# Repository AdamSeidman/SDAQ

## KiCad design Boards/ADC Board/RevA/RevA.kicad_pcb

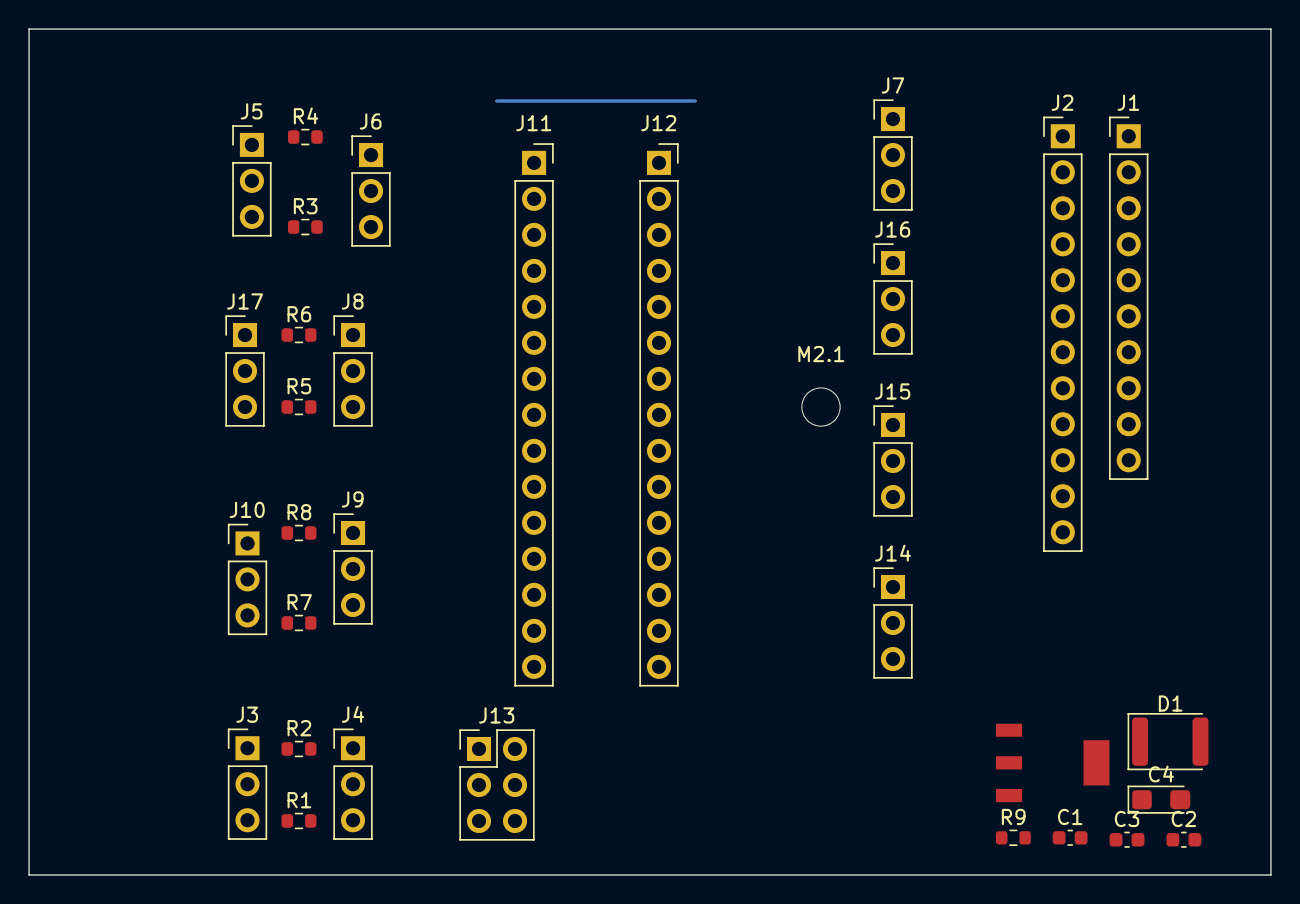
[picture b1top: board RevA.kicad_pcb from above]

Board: 2 copper layers, 87.6 x 59.7 mm, 33 parts (0 on the bottom side), 26 nets.

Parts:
C1: 0.1uF; C_0603_1608Metric
C2: 1uF; C_0603_1608Metric
C3: 1uF_cpu; C_0603_1608Metric
C4: 4.7uF_16V_cpu; CP_EIA-3216-18_Kemet-A
D1: LED; LED_1812_4532Metric
J1: Left Connector; PinHeader_1x10_P2.54mm_Vertical
J2: Right Connector; PinHeader_1x12_P2.54mm_Vertical
J3, J5, J7, J9, J14, J15, J16, J17: Screw Terminals; PinHeader_1x03_P2.54mm_Vertical
J4, J6, J8, J10: Jumper Terminals; PinHeader_1x03_P2.54mm_Vertical
J11, J12: Arduino Nano; PinSocket_1x15_P2.54mm_Vertical
J13: Extra Pins; PinHeader_2x03_P2.54mm_Vertical
M2.1: CMH; MountingHole_2.7mm_M2.5
R1, R2, R3, R4, R5, R6, R7, R8: 10k; R_0603_1608Metric
R9: 350?; R_0603_1608Metric
VR1: LM1117IMPX-5.0; SOT230P700X180-4N

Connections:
/5V: C2.1, C3.1, C4.1, J1.2, J1.4, J3.3, J5.3, J7.3, J9.3, J12.1, J13.1, J14.3, J15.3, J16.3, J17.3, R1.2, R3.2, R5.2, R7.2, VR1.2, VR1.4
/Analog_0: J12.12, J14.2
/Analog_1: J12.11, J15.2
/Analog_2: J12.10, J16.2
/Analog_3: J12.9, J17.2
/Controller/A6: J12.6, J13.3
/Controller/A7: J12.5, J13.2
/Controller/D11: J11.14, J13.4
/Controller/D12: J11.15, J13.5
/Digital_0: J3.2, J4.2, J11.5
/Digital_1: J5.2, J6.2, J11.6
/Digital_2: J7.2, J8.2, J11.7
/Digital_3: J9.2, J10.2, J11.8
/GND: C1.2, C2.2, C3.2, C4.2, D1.1, J1.6, J1.9, J2.5, J2.10, J3.1, J5.1, J7.1, J9.1, J11.4, J12.2, J13.6, J14.1, J15.1, J16.1, J17.1, R2.2, R4.2, R6.2, R8.2, VR1.1
/I2C_Clock: J1.5, J12.7
/I2C_Data: J1.3, J12.8
/VCC: C1.1, R9.1, VR1.3
unnamed: D1.2, R9.2
unnamed: J4.1, R2.1
unnamed: J4.3, R1.1
unnamed: J6.1, R4.1
unnamed: J6.3, R3.1
unnamed: J8.1, R6.1
unnamed: J8.3, R5.1
unnamed: J10.1, R8.1
unnamed: J10.3, R7.1

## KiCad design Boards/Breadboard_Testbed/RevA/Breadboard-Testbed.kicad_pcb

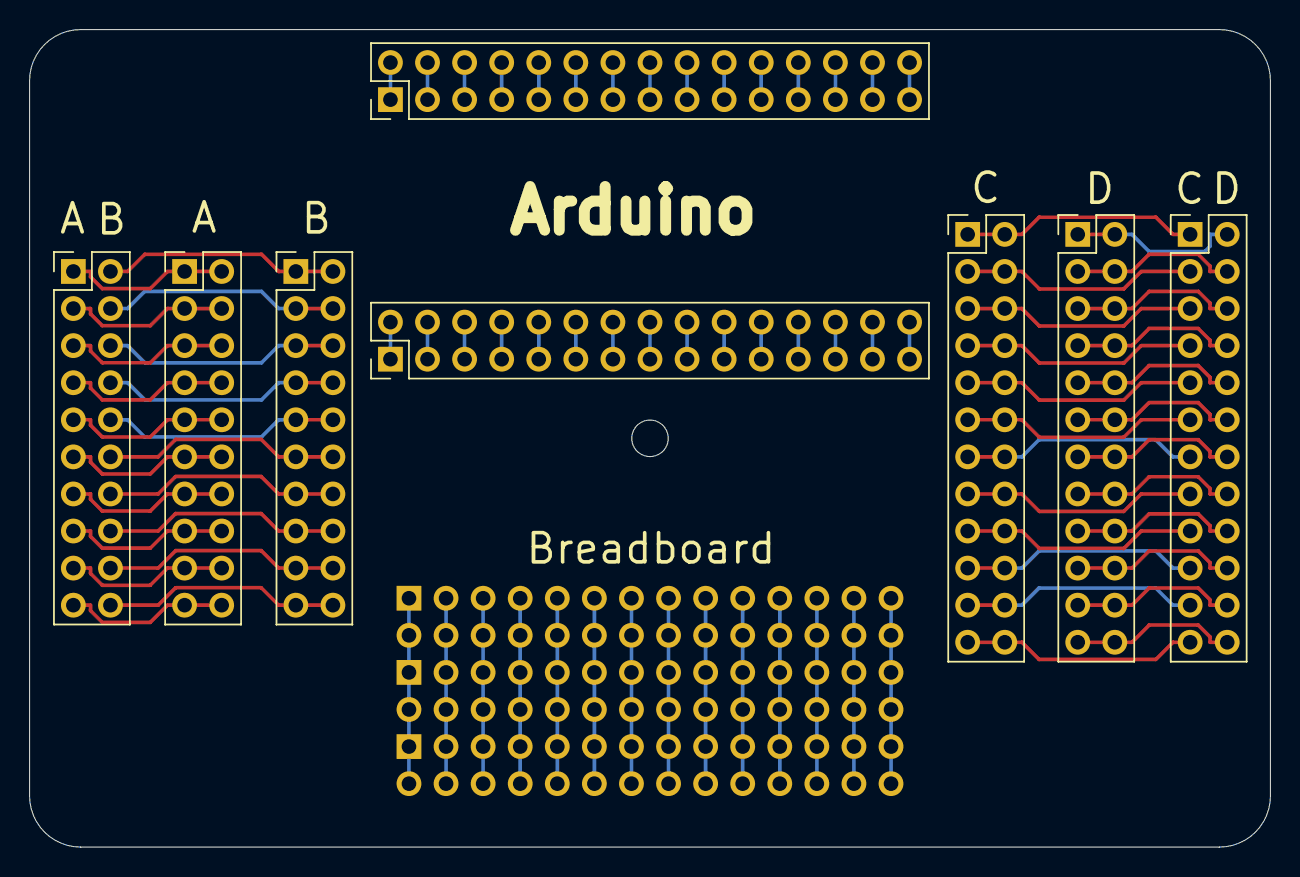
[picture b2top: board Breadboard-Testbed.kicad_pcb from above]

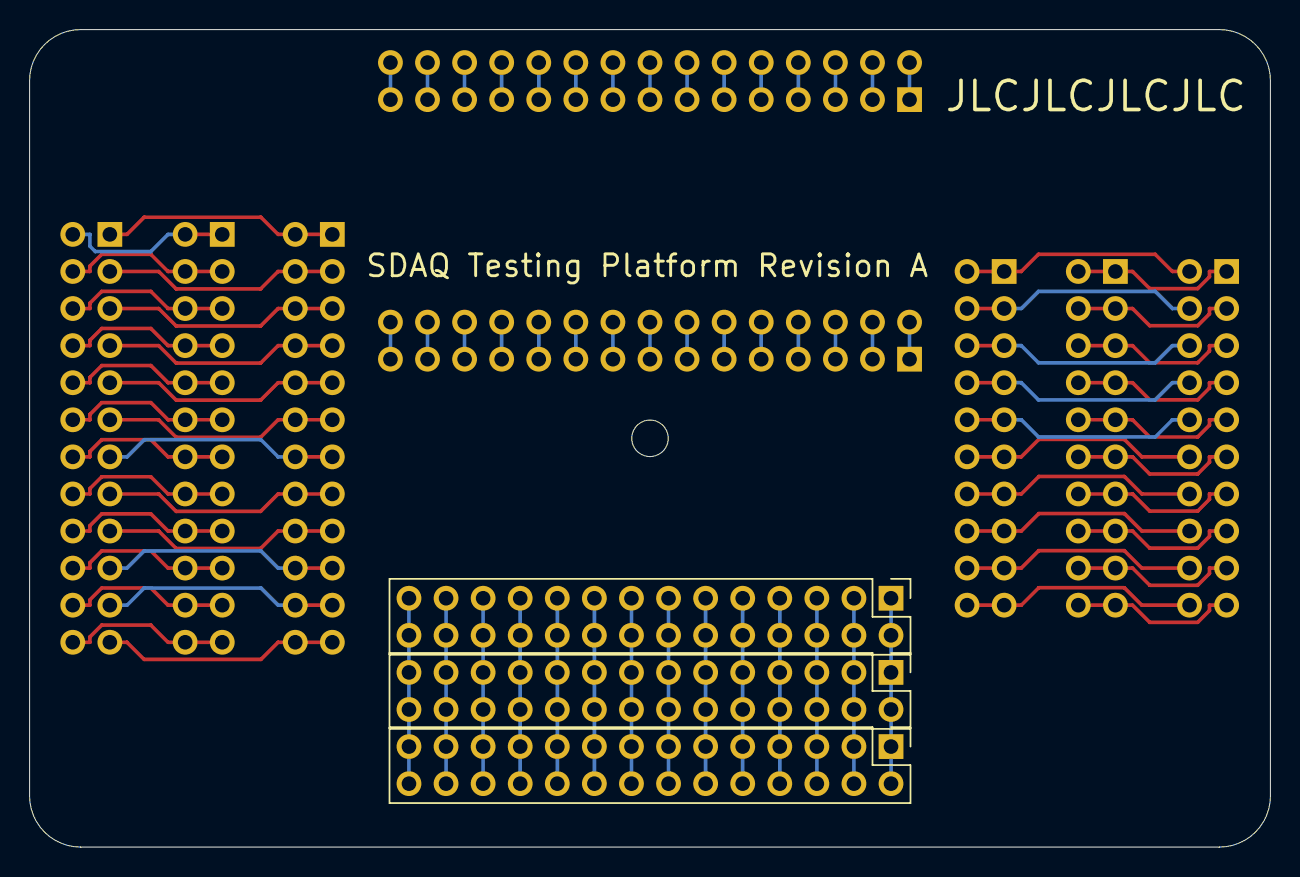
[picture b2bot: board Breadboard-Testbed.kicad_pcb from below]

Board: 2 copper layers, 85.0 x 56.0 mm, 12 parts (3 on the bottom side), 88 nets.

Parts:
H1: CMH; MountingHole_2.5mm
J1: main_conn_10; PinHeader_2x10_P2.54mm_Vertical
J2: main_conn_12; PinHeader_2x12_P2.54mm_Vertical
J3, J4, J6: Conn_02x14_Odd_Even; PinHeader_2x14_P2.54mm_Vertical
J5, J8: Conn_02x10_Counter_Clockwise; PinHeader_2x10_P2.54mm_Vertical
J7: Arduino-left; PinHeader_2x15_P2.54mm_Vertical
J9, J12: Conn_02x12_Counter_Clockwise; PinHeader_2x12_P2.54mm_Vertical
J10: Arduino-right; PinHeader_2x15_P2.54mm_Vertical

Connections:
unnamed: J1.1, J5.1, J5.2
unnamed: J1.2, J8.1, J8.2
unnamed: J1.3, J5.3, J5.4
unnamed: J1.4, J8.3, J8.4
unnamed: J1.5, J5.5, J5.6
unnamed: J1.6, J8.5, J8.6
unnamed: J1.7, J5.7, J5.8
unnamed: J1.8, J8.7, J8.8
unnamed: J1.9, J5.9, J5.10
unnamed: J1.10, J8.9, J8.10
unnamed: J1.11, J5.11, J5.12
unnamed: J1.12, J8.11, J8.12
unnamed: J1.13, J5.13, J5.14
unnamed: J1.14, J8.13, J8.14
unnamed: J1.15, J5.15, J5.16
unnamed: J1.16, J8.15, J8.16
unnamed: J1.17, J5.17, J5.18
unnamed: J1.18, J8.17, J8.18
unnamed: J1.19, J5.19, J5.20
unnamed: J1.20, J8.19, J8.20
unnamed: J2.1, J9.1, J9.2
unnamed: J2.3, J9.3, J9.4
unnamed: J2.5, J9.5, J9.6
unnamed: J2.7, J9.7, J9.8
unnamed: J2.9, J9.9, J9.10
unnamed: J2.11, J9.11, J9.12
unnamed: J2.13, J9.13, J9.14
unnamed: J2.15, J9.15, J9.16
unnamed: J2.17, J9.17, J9.18
unnamed: J2.19, J9.19, J9.20
unnamed: J2.21, J9.21, J9.22
unnamed: J2.23, J9.23, J9.24
unnamed: J3.1, J3.2, J4.1, J4.2, J6.1, J6.2
unnamed: J3.3, J3.4, J4.3, J4.4, J6.3, J6.4
unnamed: J3.5, J3.6, J4.5, J4.6, J6.5, J6.6
unnamed: J3.7, J3.8, J4.7, J4.8, J6.7, J6.8
unnamed: J3.9, J3.10, J4.9, J4.10, J6.9, J6.10
unnamed: J3.11, J3.12, J4.11, J4.12, J6.11, J6.12
unnamed: J3.13, J3.14, J4.13, J4.14, J6.13, J6.14
unnamed: J3.15, J3.16, J4.15, J4.16, J6.15, J6.16
unnamed: J3.17, J3.18, J4.17, J4.18, J6.17, J6.18
unnamed: J3.19, J3.20, J4.19, J4.20, J6.19, J6.20
unnamed: J3.21, J3.22, J4.21, J4.22, J6.21, J6.22
unnamed: J3.23, J3.24, J4.23, J4.24, J6.23, J6.24
unnamed: J3.25, J3.26, J4.25, J4.26, J6.25, J6.26
unnamed: J3.27, J3.28, J4.27, J4.28, J6.27, J6.28
unnamed: J7.1, J7.2
unnamed: J7.3, J7.4
unnamed: J7.5, J7.6
unnamed: J7.7, J7.8
unnamed: J7.9, J7.10
unnamed: J7.11, J7.12
unnamed: J7.13, J7.14
unnamed: J7.15, J7.16
unnamed: J7.17, J7.18
unnamed: J7.19, J7.20
unnamed: J7.21, J7.22
unnamed: J7.23, J7.24
unnamed: J7.25, J7.26
unnamed: J7.27, J7.28
unnamed: J7.29, J7.30
unnamed: J10.1, J10.2
unnamed: J10.3, J10.4
unnamed: J10.5, J10.6
unnamed: J10.7, J10.8
unnamed: J10.9, J10.10
unnamed: J10.11, J10.12
unnamed: J10.13, J10.14
unnamed: J10.15, J10.16
unnamed: J10.17, J10.18
unnamed: J10.19, J10.20
unnamed: J10.21, J10.22
unnamed: J10.23, J10.24
unnamed: J10.25, J10.26
unnamed: J10.27, J10.28
unnamed: J10.29, J10.30
unnamed: J2.2, J12.1, J12.2
unnamed: J2.4, J12.3, J12.4
unnamed: J2.6, J12.5, J12.6
unnamed: J2.8, J12.7, J12.8
unnamed: J2.10, J12.9, J12.10
unnamed: J2.12, J12.11, J12.12
unnamed: J2.14, J12.13, J12.14
unnamed: J2.16, J12.15, J12.16
unnamed: J2.18, J12.17, J12.18
unnamed: J2.20, J12.19, J12.20
unnamed: J2.22, J12.21, J12.22
unnamed: J2.24, J12.23, J12.24

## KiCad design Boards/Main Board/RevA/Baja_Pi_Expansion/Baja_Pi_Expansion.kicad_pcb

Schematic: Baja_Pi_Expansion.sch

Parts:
J1: Conn_02x10_Counter_Clockwise; PinHeader_2x10_P2.54mm_Vertical
J2: Conn_02x12_Counter_Clockwise; PinHeader_2x12_P2.54mm_Vertical
J3: Screw_Terminal_01x04; PinHeader_1x04_P2.54mm_Vertical
J4: Conn_02x20_Odd_Even; PinHeader_2x20_P2.54mm_Vertical
J5: Conn_01x03_Male; PinHeader_1x03_P2.54mm_Vertical
J6: Screw_Terminal_01x06; PinHeader_1x06_P2.54mm_Vertical
R1, R2: 4.7k; R_0603_1608Metric
R3, R4, R5, R6: R_US; R_0603_1608Metric
U1: HDSP-7403; HDSP-7401

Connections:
/3v3: J1.1, J1.17, J4.1, J4.17
/5v: J1.2, J1.4, J4.2, J4.4, J5.1, J6.1, J6.4, R1.1, R2.2, R5.1; also elsewhere on the board
/analog_in: J2.9, J4.29, J6.5
/brakes: J6.7, R3.1
/dig_in: J2.11, J4.31, J5.2, J6.2, R5.2, R6.1
/gnd: J1.6, J1.9, J1.14, J1.20, J2.5, J2.10, J2.14, J2.19, J3.2, J3.4, J4.6, J4.9, J4.14, J4.20, J4.25, J4.30, J4.34, J4.39, J5.3, J6.3, J6.6, R4.2, R6.2, U1.1 (CC), U1.6 (CC); also elsewhere on the board
/gpio1: J1.7, J4.7, R3.2, R4.1
/gpio4: J2.12, J4.32, U1.7 (DP)
/gpio5: J2.13, J4.33, U1.3 (G)
/gpio6: J1.15, J4.15, U1.2 (F)
/gpio7: J1.16, J4.16, U1.4 (E)
/gpio8: J1.18, J4.18, U1.5 (D)
/gpio9: J2.2, J4.22, U1.8 (C)
/gpio10: J2.17, J4.37, U1.9 (B)
/gpio11: J1.13, J4.13, U1.10 (A)
/miso: J2.1, J4.21
/miso2: J2.18, J4.38
/miso2_pwm: J2.15, J4.35
/mosi: J1.19, J4.19
/scl: J2.8, J4.28
/scl2: J1.5, J4.5, R2.1
/sclk: J2.3, J4.23
/sclk2: J2.20, J4.40
/sda: J2.7, J4.27
/sda2: J1.3, J4.3, R1.2
/spi2_ce0: J1.12, J4.12
/spi2_ce1: J1.11, J4.11
/spi_ce0: J2.4, J4.24
/spi_ce1: J2.6, J4.26
/uart_rx: J1.10, J4.10
/uart_tx: J1.8, J4.8
/vcc: J2.23, J2.24, J3.1, J3.3; also elsewhere on the board

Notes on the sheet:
pwm
gpio 14
gpio 15
gpio 17
gpio 8
gpio 7
gpio 1
12 pwm
gpio 16
gpio 20
gpio 21
gpio 10 gpio 9 gpio 11
gpio 0
gpio 11
gpio 10
gpio 9
+20
pwm 12
pin jumper

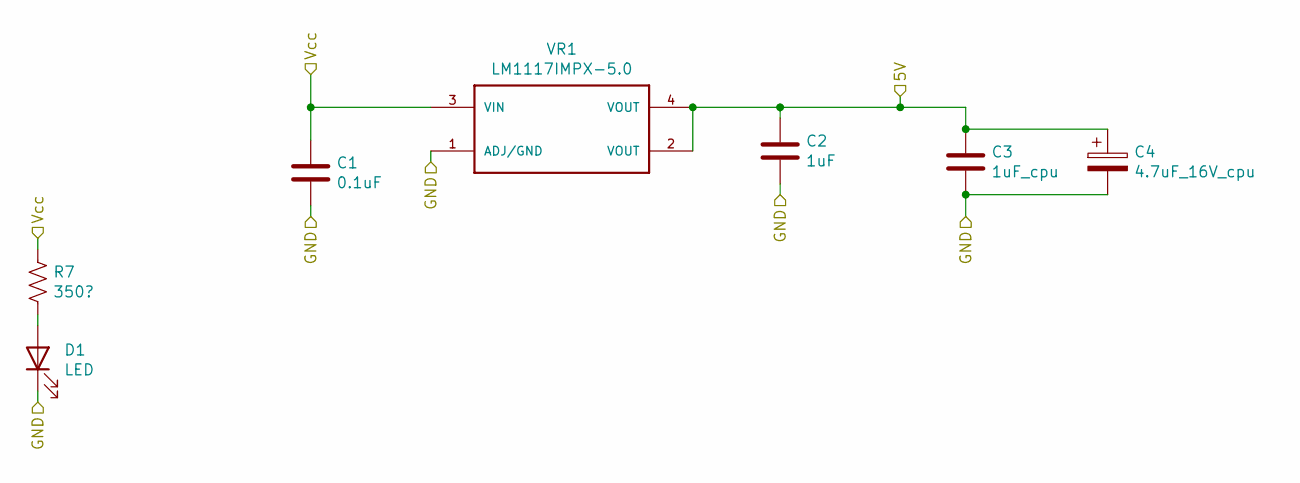
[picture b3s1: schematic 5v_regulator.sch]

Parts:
C1: 0.1uF; C_0603_1608Metric
C2: 1uF; C_0603_1608Metric
C3: 1uF_cpu; C_0603_1608Metric
C4: 4.7uF_16V_cpu
D1: LED; LED_1812_4532Metric
R7: 350?; R_0603_1608Metric
VR1: LM1117IMPX-5.0

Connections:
/5v: C2.1, C3.1, C4.1, VR1.2 (VOUT), VR1.4 (VOUT); also elsewhere on the board
/gnd: C1.2, C2.2, C3.2, C4.2, D1.1 (K), VR1.1 (ADJ/GND); also elsewhere on the board
/vcc: C1.1, R7.1, VR1.3 (VIN); also elsewhere on the board
unnamed: D1.2 (A), R7.2

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
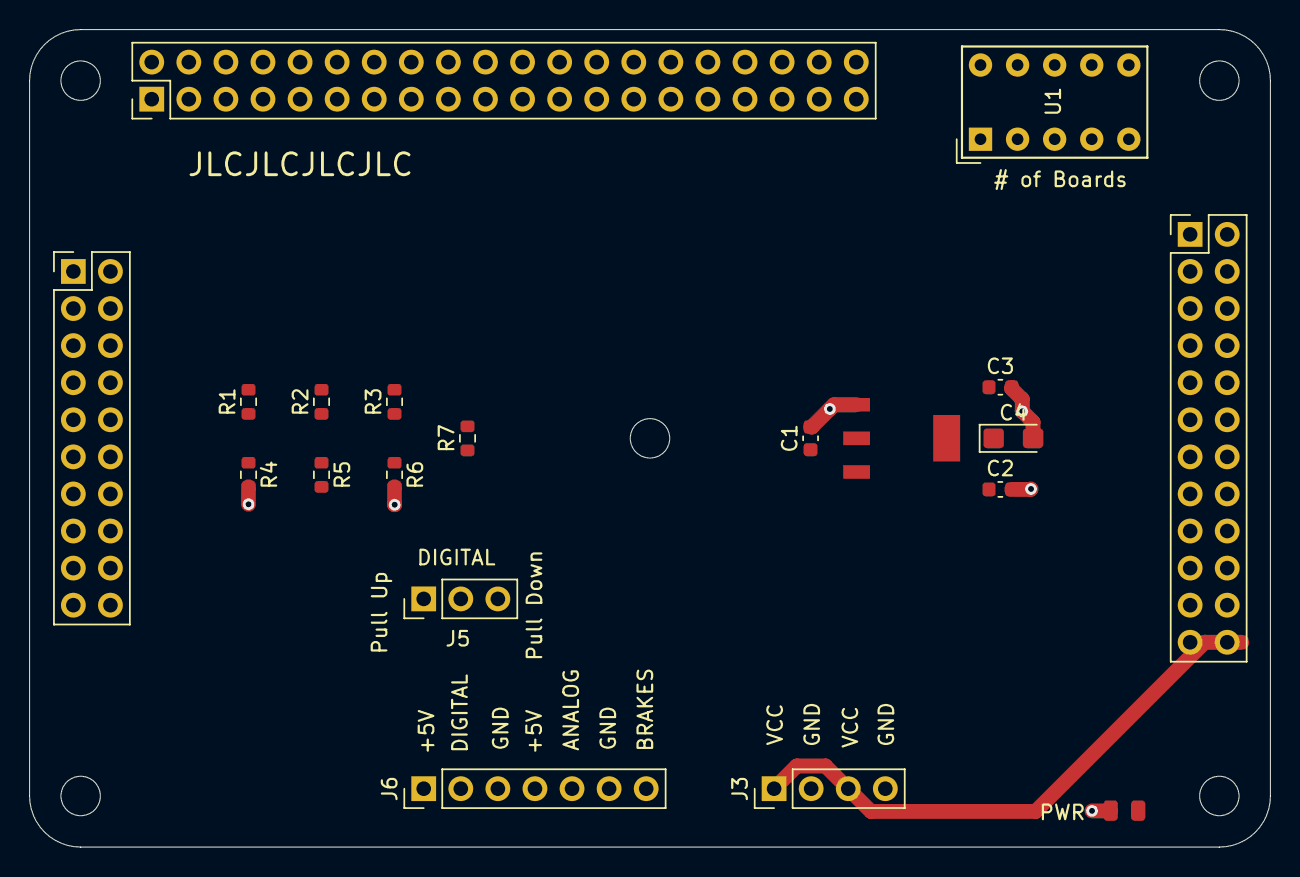
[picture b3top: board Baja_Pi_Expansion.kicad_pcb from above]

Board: 2 copper layers, 85.0 x 56.0 mm, 25 parts (0 on the bottom side), 34 nets.

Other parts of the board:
H1: MH1; MountingHole_2.7mm_M2.5
H2: MH2; MountingHole_2.7mm_M2.5
H3: MH3; MountingHole_2.7mm_M2.5
H4: MH4; MountingHole_2.7mm_M2.5
H5: MH_c; MountingHole_2.7mm_M2.5
